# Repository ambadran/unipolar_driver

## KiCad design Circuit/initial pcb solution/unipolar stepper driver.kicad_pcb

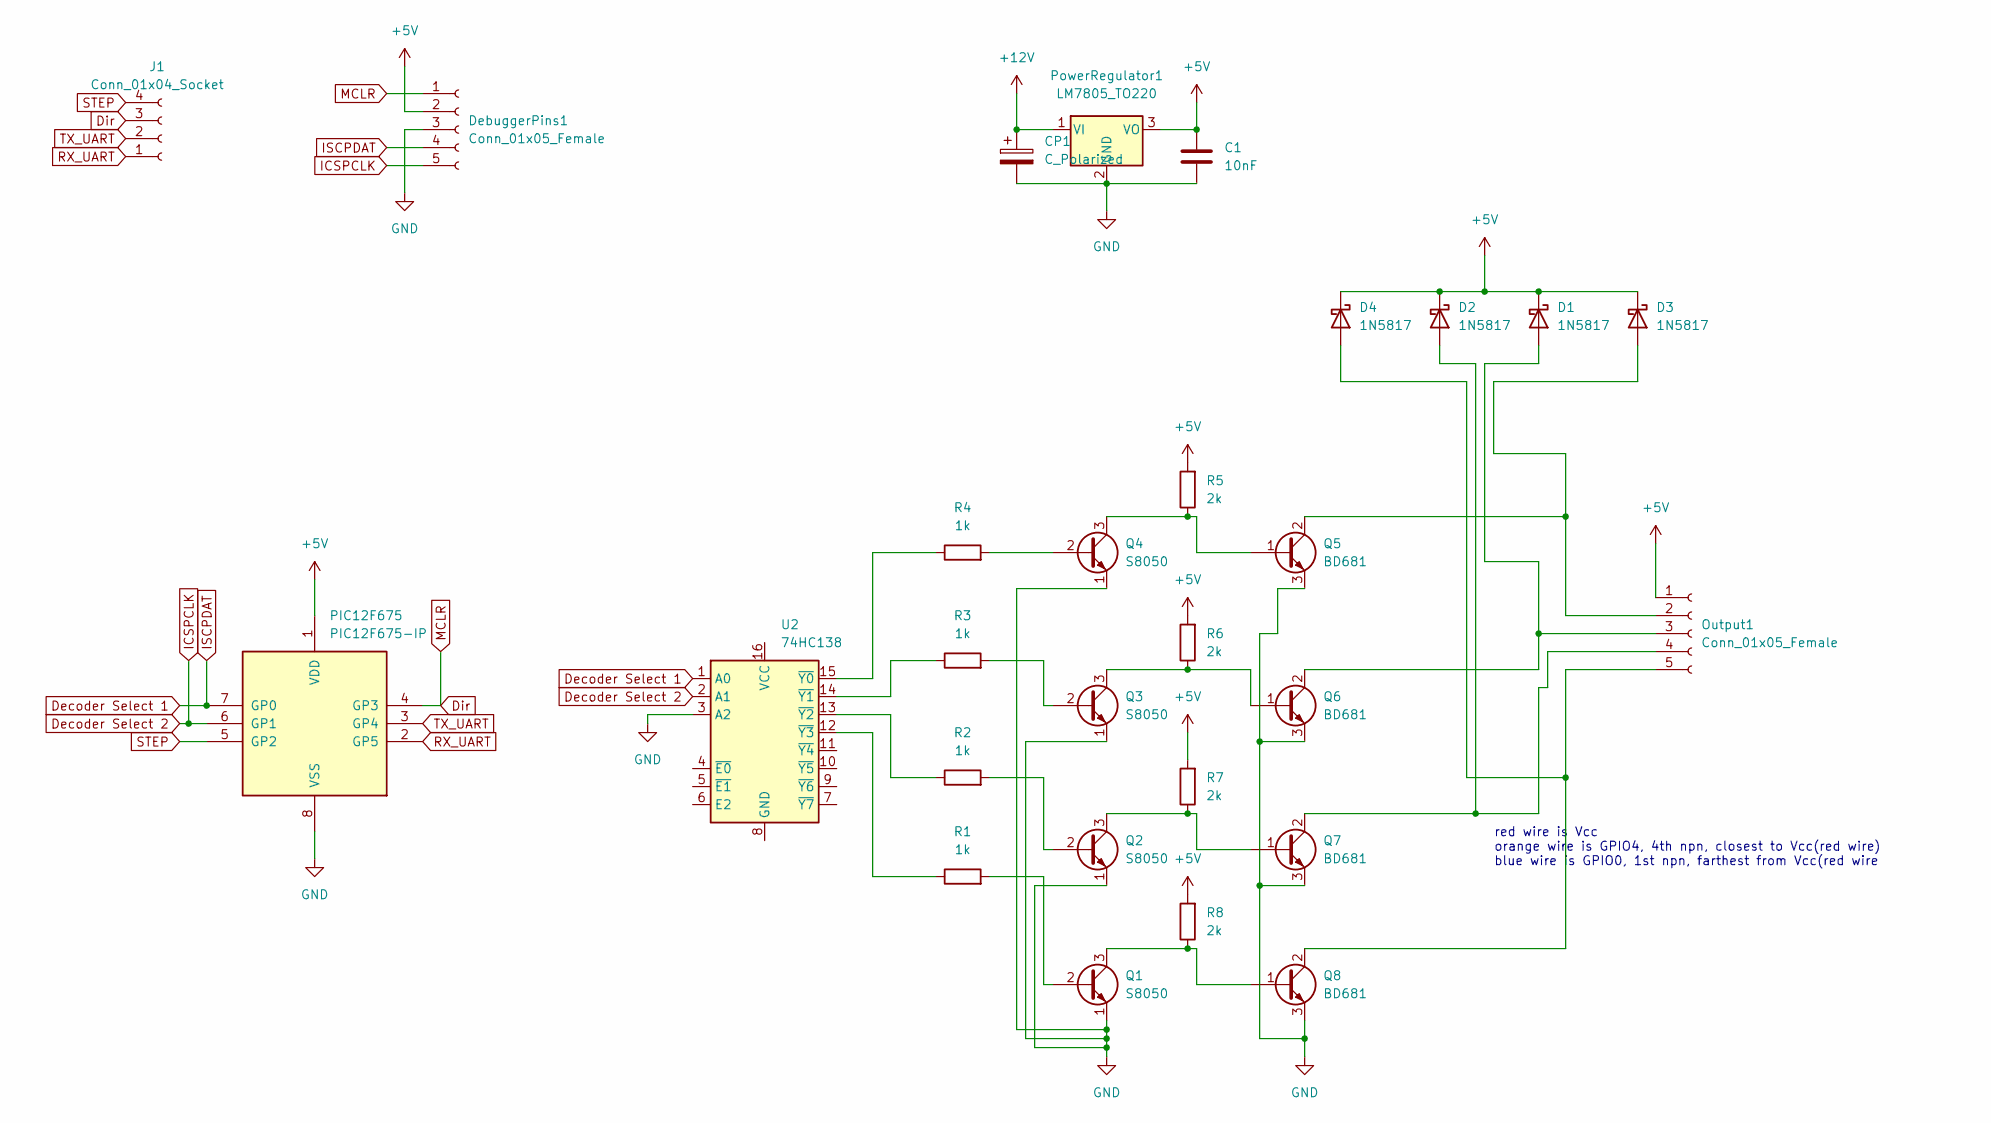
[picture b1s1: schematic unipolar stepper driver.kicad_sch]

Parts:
C1: 10nF; C_Disc_D3.0mm_W2.0mm_P2.50mm
CP1: C_Polarized; CP_Radial_D5.0mm_P2.50mm
D1, D2, D3, D4: 1N5817; D_DO-34_SOD68_P7.62mm_Horizontal
DebuggerPins1: Conn_01x05_Female; PinHeader_1x05_P2.54mm_Vertical
J1: Conn_01x04_Socket; PinSocket_1x04_P2.54mm_Vertical
Output1: Conn_01x05_Female; PinHeader_1x05_P2.54mm_Vertical
PIC12F675: PIC12F675-IP; DIP-8_W7.62mm
PowerRegulator1: LM7805_TO220; TO-220-3_Vertical
Q1, Q2, Q3, Q4: S8050; TO-92_Inline
Q5, Q6, Q7, Q8: BD681; TO-126-3_Vertical
R1, R2, R3, R4: 1k; R_Axial_DIN0207_L6.3mm_D2.5mm_P7.62mm_Horizontal
R5, R6, R7, R8: 2k; R_Axial_DIN0207_L6.3mm_D2.5mm_P10.16mm_Horizontal
U2: 74HC138; DIP-16_W7.62mm_LongPads

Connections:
+5V: C1.2, D1.1 (K), D2.1 (K), D3.1 (K), D4.1 (K), DebuggerPins1.2, Output1.1, PIC12F675.1 (VDD), PowerRegulator1.3 (VO), R5.2, R6.2, R7.2, R8.2
+12V: CP1.1, PowerRegulator1.1 (VI)
Decoder Select 1: DebuggerPins1.4, PIC12F675.7 (GP0), U2.1 (A0)
Decoder Select 2: DebuggerPins1.5, PIC12F675.6 (GP1), U2.2 (A1)
Dir: DebuggerPins1.1, J1.3, PIC12F675.4 (GP3)
GND: C1.1, CP1.2, DebuggerPins1.3, PIC12F675.8 (VSS), PowerRegulator1.2 (GND), Q1.1 (E), Q2.1 (E), Q3.1 (E), Q4.1 (E), Q5.3 (E), Q6.3 (E), Q7.3 (E), Q8.3 (E), U2.3 (A2)
unnamed: D1.2 (A), Output1.3, Q6.2 (C)
unnamed: D2.2 (A), Output1.4, Q7.2 (C)
unnamed: D3.2 (A), Output1.2, Q5.2 (C)
unnamed: D4.2 (A), Output1.5, Q8.2 (C)
unnamed: Q1.2 (B), R1.2
unnamed: Q1.3 (C), Q8.1 (B), R8.1
unnamed: Q2.2 (B), R2.2
unnamed: Q2.3 (C), Q7.1 (B), R7.1
unnamed: Q3.2 (B), R3.2
unnamed: Q3.3 (C), Q6.1 (B), R6.1
unnamed: Q4.2 (B), R4.2
unnamed: Q4.3 (C), Q5.1 (B), R5.1
unnamed: R4.1, U2.15 (~Y0)
unnamed: R3.1, U2.14 (~Y1)
unnamed: R2.1, U2.13 (~Y2)
unnamed: R1.1, U2.12 (~Y3)
RX_UART: J1.1, PIC12F675.2 (GP5)
STEP: J1.4, PIC12F675.5 (GP2)
TX_UART: J1.2, PIC12F675.3 (GP4)

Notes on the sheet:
red wire is Vcc orange wire is GPIO4, 4th npn, closest to Vcc(red wire) blue wire is GPIO0, 1st npn, farthest from Vcc(red wire

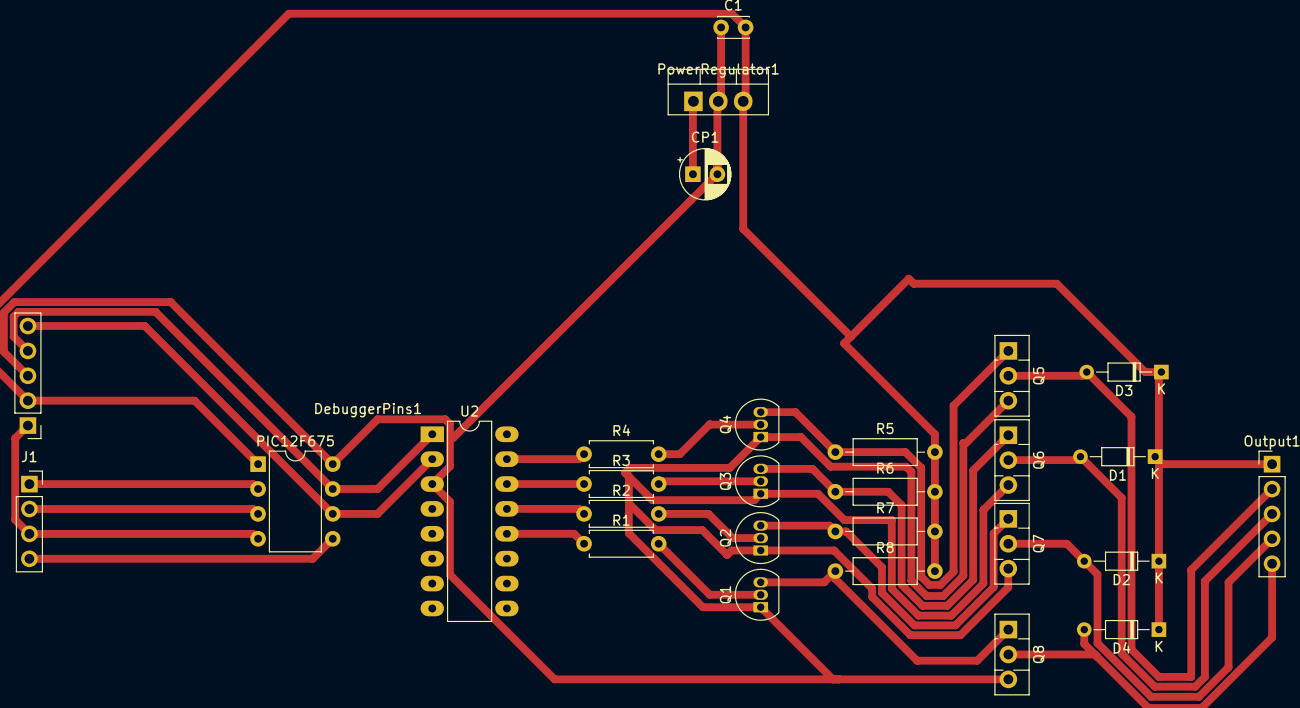
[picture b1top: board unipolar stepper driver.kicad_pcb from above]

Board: 2 copper layers, 28 parts (0 on the bottom side), 25 nets.

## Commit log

2023-11-06 Added circuit schematic and Pic microcontroller code
2023-11-08 Developed V2 Circuit schematic AND PCB
